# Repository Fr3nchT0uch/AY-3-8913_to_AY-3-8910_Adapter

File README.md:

# AY-3-8913 to AY-3-8910 Adapter

A simple adapter to replace the AY-3-8913 with the AY-3-8910 (or the YM2149)

## Why to replace the AY-3-8913 ?
If you've read this article https://www.fenarinarsa.com/?p=3183, you know that there's a chance your Mockingboard with AY-3-8913 will sound *weird* under certain circumstances.

Here a short video to hear the difference between a faulty AY-3-8913 and an AY-3-8910 in action (featuring Digidream 2): https://www.youtube.com/watch?v=_qslugOY2Dw

That's why we decided to do an adapter to easily replace the AY-3-8913 with the AY-3-8910 (or the YM2149) which does not suffer from the same issue and is more readily available.
We have made several designs giving you the choice for your use!
And they can of course be used as a basis for your own project! 

**Note about the Phasor Card**: these adapters are designed to be used primarily on a *Mockingboard*. For the *Phasor*, as there are 4 AY-3-8913s potentially to be replaced, it will probably be necessary to use a *daughter board* as adapter. This is beyond the scope of this project (for now...)

## Credits:  
Original idea: French Touch (grouik/fenarinarsa)  
http://fr3nch.t0uch.free.fr/  
Final design (and all the hard work!): Mr Jean-Fred  
https://github.com/Jean-Fred64

*French Touch would especially like to thank Mr Jean-Fred, without whom this project would never have been possible. It's thanks to him that an embryonic schematic was transformed into a viable project!*

## License:
GNU GENERAL PUBLIC LICENSE 3

## Reference:
Datasheets:  
AY-3-8910: https://map.grauw.nl/resources/sound/generalinstrument_ay-3-8910.pdf  
YM2149: http://www.ym2149.com/ym2149.pdf  

Mockingboard Info:  
https://en.wikipedia.org/wiki/Mockingboard
https://www.reactivemicro.com/product/mockingboard-assembled-or-kit/

Manufacturing PCB:  
https://www.kicad.org/  
https://jlcpcb.com/  
https://www.pcbway.com/

----  
## PCB designs:

## "Angle" version for Mockingboard (Two different PCBs for each AY-3-8913)

**LEFT** for *top* AY-3-8913:

**RIGHT** for *bottom* AY-3-8913:

- to replace one or **two** AY-3-8913 on your Mockingboard.
- you must use each version for the TOP and BOTTOM AY-3-8913 on your Mockbingboard.
- note: pay attention to the insertion direction of the AY-3-8910 on the adapter.

----  

## "Triangle" version for Mockingboard (A single PCB for the two AY-3-8913s)

- alternative (and ultimate) version to replace the TWO AY-3-8913 on the Mockingboard on the same board.

----
## "Normal" general version

- to replace only **one** AY-3-8913 on the Mockingboard (the **bottom** one only!).
- to replace the AY-3-8913 on other machines (for example: some old Pinball *soundcards*).
- note: pay attention to the insertion direction of the AY-3-8910 on the adapter.

- **WARNING**: do not use this model if you want to replace the **TWO** AY-3-8913s on your Mockingboard because you will not be able to close the Apple II cover! Use the other designs instead!

## Audio Output:

Each PCD design has an **Audio Output** (pins) for direct connection to the AY-3-8910/YM2149 without using the Mockingboard amplification part. This allows for much better quality with a line level output.

To be heard here: https://www.youtube.com/watch?v=SWxKD_74ifs

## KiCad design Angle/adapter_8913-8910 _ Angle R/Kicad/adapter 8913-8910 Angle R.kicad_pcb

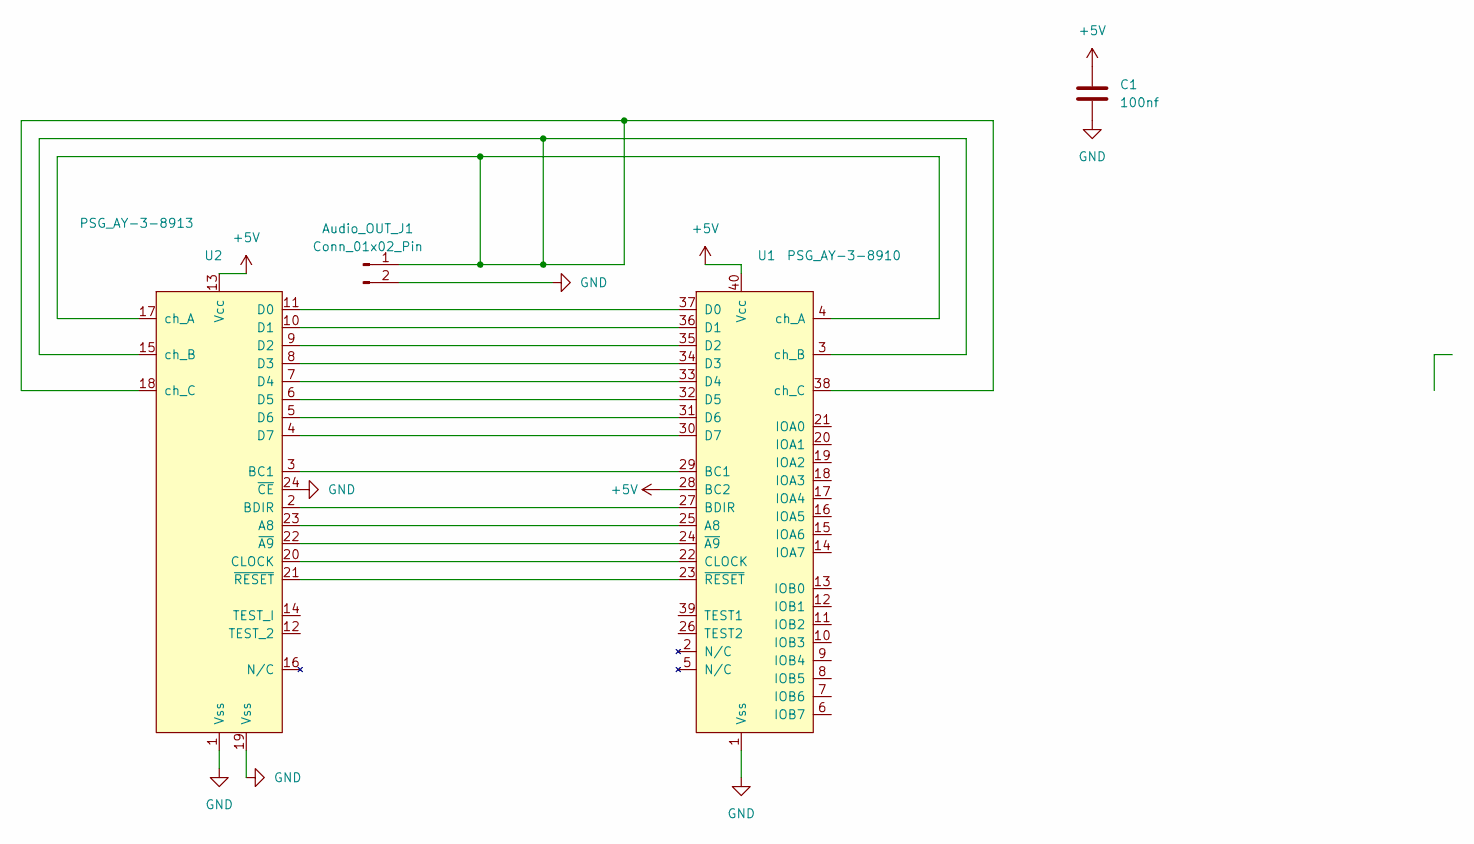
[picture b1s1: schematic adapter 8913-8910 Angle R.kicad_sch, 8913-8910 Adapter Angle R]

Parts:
Audio_OUT_J1: Conn_01x02_Pin; PinHeader_1x02_P2.54mm_Vertical
C1: 100nf; C_0805_2012Metric_Pad1.18x1.45mm_HandSolder
U1: PSG_AY-3-8910; DIP-40_W15.24mm_Socket
U2: PSG_AY-3-8913; DIP-24_W15.24mm_LongPads

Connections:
+5V: C1.1, U1.28 (BC2), U1.40 (Vcc), U2.13 (Vcc)
GND: Audio_OUT_J1.2, C1.2, U1.1 (Vss), U2.1 (Vss), U2.19 (Vss), U2.24 (~CE)
unnamed: Audio_OUT_J1.1, U1.3 (ch_B), U1.4 (ch_A), U1.38 (ch_C), U2.15 (ch_B), U2.17 (ch_A), U2.18 (ch_C)
unnamed: U1.25 (A8), U2.23 (A8)
unnamed: U1.29 (BC1), U2.3 (BC1)
unnamed: U1.27 (BDIR), U2.2 (BDIR)
unnamed: U1.22 (CLOCK), U2.20 (CLOCK)
unnamed: U1.37 (D0), U2.11 (D0)
unnamed: U1.36 (D1), U2.10 (D1)
unnamed: U1.35 (D2), U2.9 (D2)
unnamed: U1.34 (D3), U2.8 (D3)
unnamed: U1.33 (D4), U2.7 (D4)
unnamed: U1.32 (D5), U2.6 (D5)
unnamed: U1.31 (D6), U2.5 (D6)
unnamed: U1.30 (D7), U2.4 (D7)
unnamed: U1.24 (~A9), U2.22 (~A9)
unnamed: U1.23 (~RESET), U2.21 (~RESET)

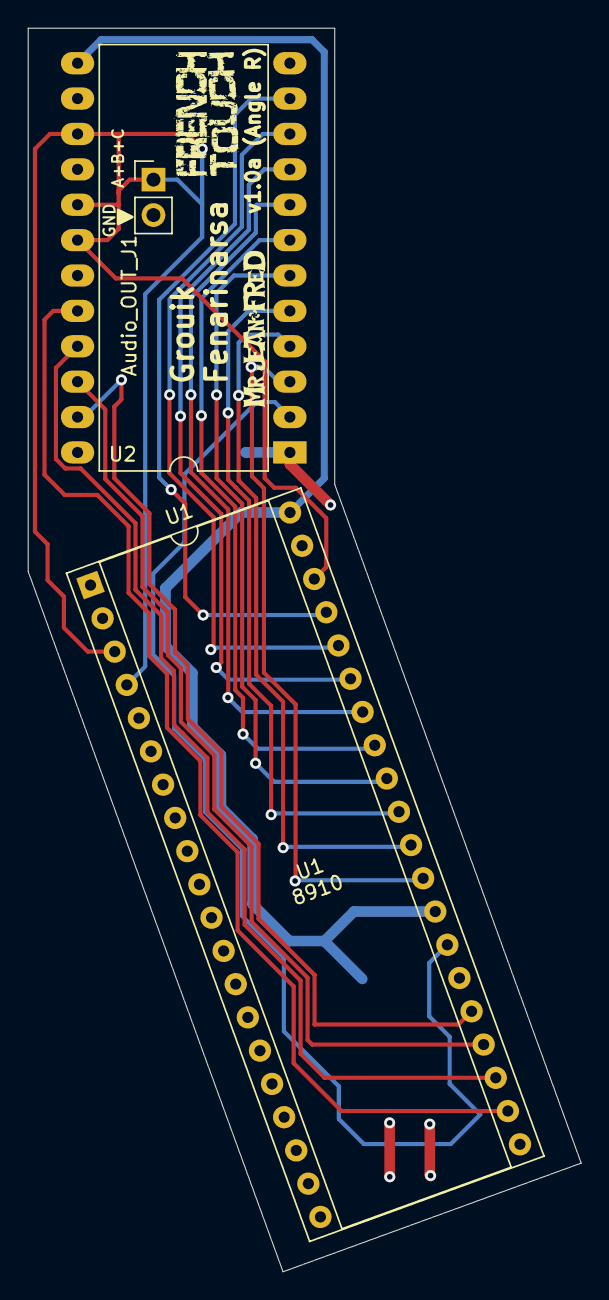
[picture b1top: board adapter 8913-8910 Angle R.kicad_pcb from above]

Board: 2 copper layers, 39.7 x 89.3 mm, 4 parts (1 on the bottom side), 17 nets.

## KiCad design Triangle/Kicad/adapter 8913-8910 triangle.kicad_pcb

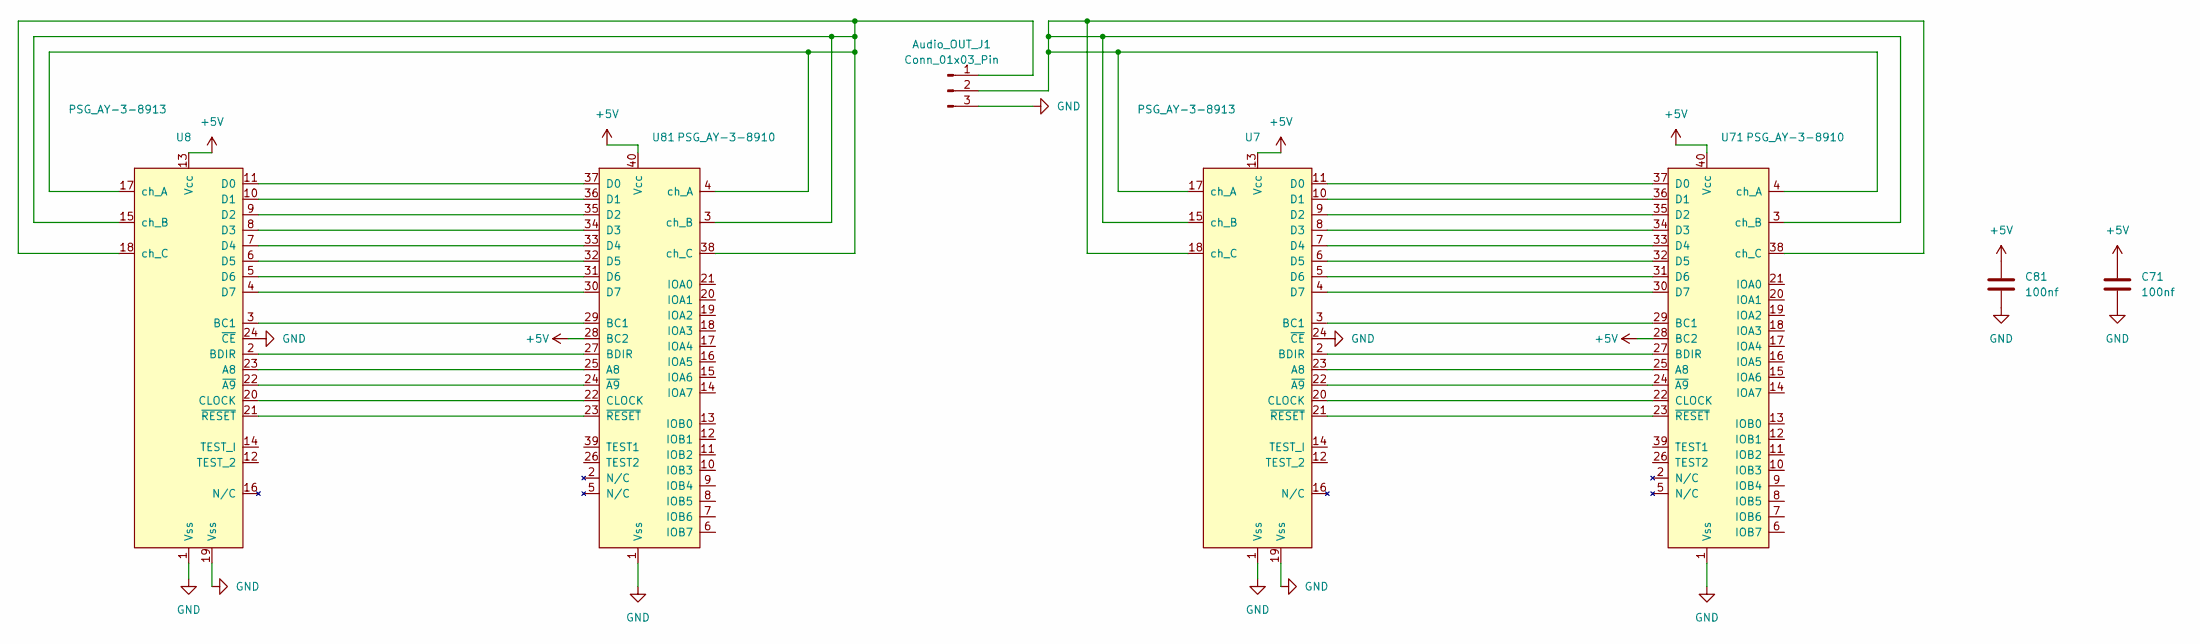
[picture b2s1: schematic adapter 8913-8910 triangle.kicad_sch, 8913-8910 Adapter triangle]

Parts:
Audio_OUT_J1: Conn_01x03_Pin; PinHeader_1x03_P2.54mm_Horizontal
C71, C81: 100nf; C_0805_2012Metric_Pad1.18x1.45mm_HandSolder
U7, U8: PSG_AY-3-8913; DIP-24_W15.24mm_LongPads
U71, U81: PSG_AY-3-8910; DIP-40_W15.24mm_Socket

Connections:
+5V: C71.1, C81.1, U7.13 (Vcc), U8.13 (Vcc), U71.28 (BC2), U71.40 (Vcc), U81.28 (BC2), U81.40 (Vcc)
GND: Audio_OUT_J1.3, C71.2, C81.2, U7.1 (Vss), U7.19 (Vss), U7.24 (~CE), U8.1 (Vss), U8.19 (Vss), U8.24 (~CE), U71.1 (Vss), U81.1 (Vss)
unnamed: Audio_OUT_J1.1, U8.15 (ch_B), U8.17 (ch_A), U8.18 (ch_C), U81.3 (ch_B), U81.4 (ch_A), U81.38 (ch_C)
unnamed: Audio_OUT_J1.2, U7.15 (ch_B), U7.17 (ch_A), U7.18 (ch_C), U71.3 (ch_B), U71.4 (ch_A), U71.38 (ch_C)
unnamed: U7.23 (A8), U71.25 (A8)
unnamed: U7.3 (BC1), U71.29 (BC1)
unnamed: U7.2 (BDIR), U71.27 (BDIR)
unnamed: U7.20 (CLOCK), U71.22 (CLOCK)
unnamed: U7.11 (D0), U71.37 (D0)
unnamed: U7.10 (D1), U71.36 (D1)
unnamed: U7.9 (D2), U71.35 (D2)
unnamed: U7.8 (D3), U71.34 (D3)
unnamed: U7.7 (D4), U71.33 (D4)
unnamed: U7.6 (D5), U71.32 (D5)
unnamed: U7.5 (D6), U71.31 (D6)
unnamed: U7.4 (D7), U71.30 (D7)
unnamed: U7.22 (~A9), U71.24 (~A9)
unnamed: U7.21 (~RESET), U71.23 (~RESET)
unnamed: U8.23 (A8), U81.25 (A8)
unnamed: U8.3 (BC1), U81.29 (BC1)
unnamed: U8.2 (BDIR), U81.27 (BDIR)
unnamed: U8.20 (CLOCK), U81.22 (CLOCK)
unnamed: U8.11 (D0), U81.37 (D0)
unnamed: U8.10 (D1), U81.36 (D1)
unnamed: U8.9 (D2), U81.35 (D2)
unnamed: U8.8 (D3), U81.34 (D3)
unnamed: U8.7 (D4), U81.33 (D4)
unnamed: U8.6 (D5), U81.32 (D5)
unnamed: U8.5 (D6), U81.31 (D6)
unnamed: U8.4 (D7), U81.30 (D7)
unnamed: U8.22 (~A9), U81.24 (~A9)
unnamed: U8.21 (~RESET), U81.23 (~RESET)

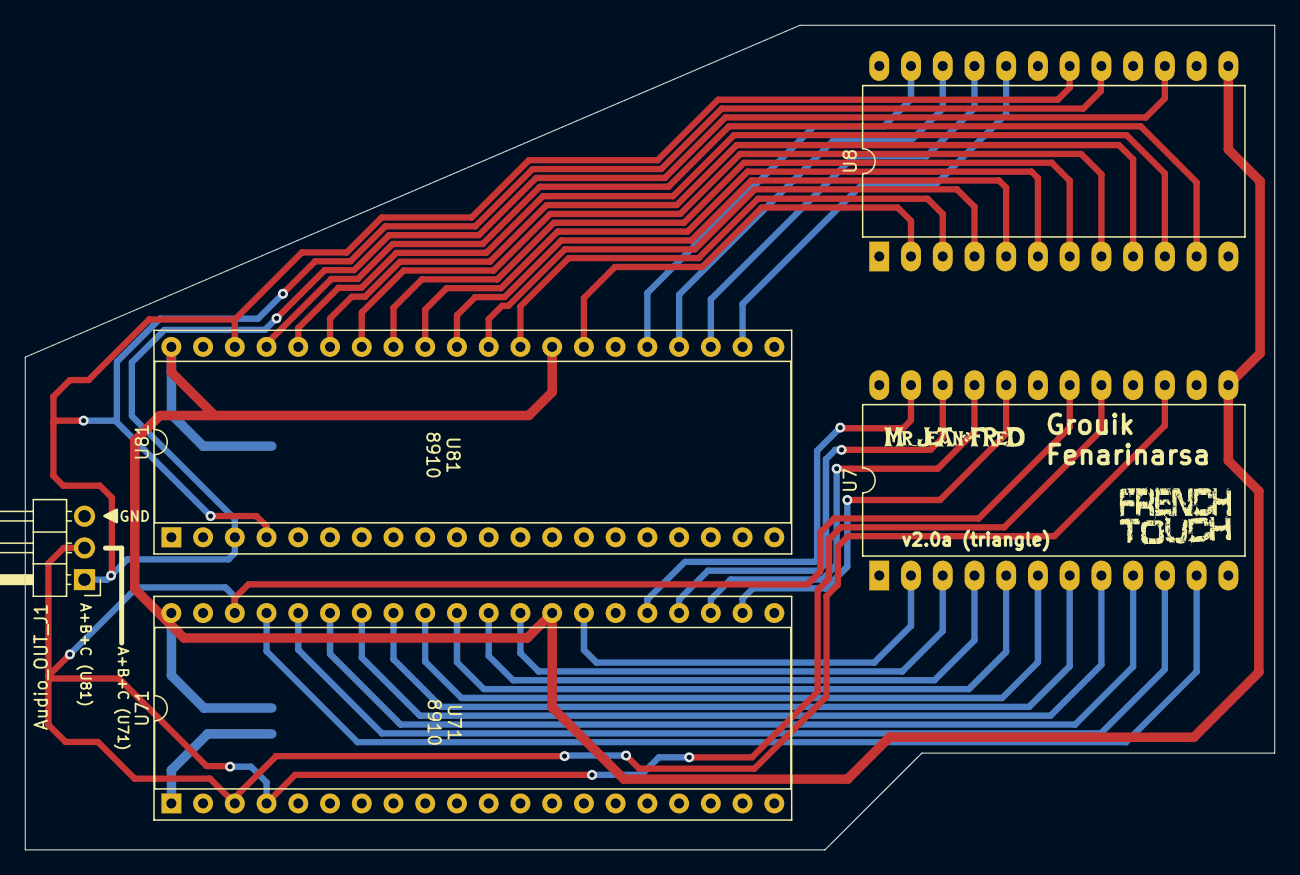
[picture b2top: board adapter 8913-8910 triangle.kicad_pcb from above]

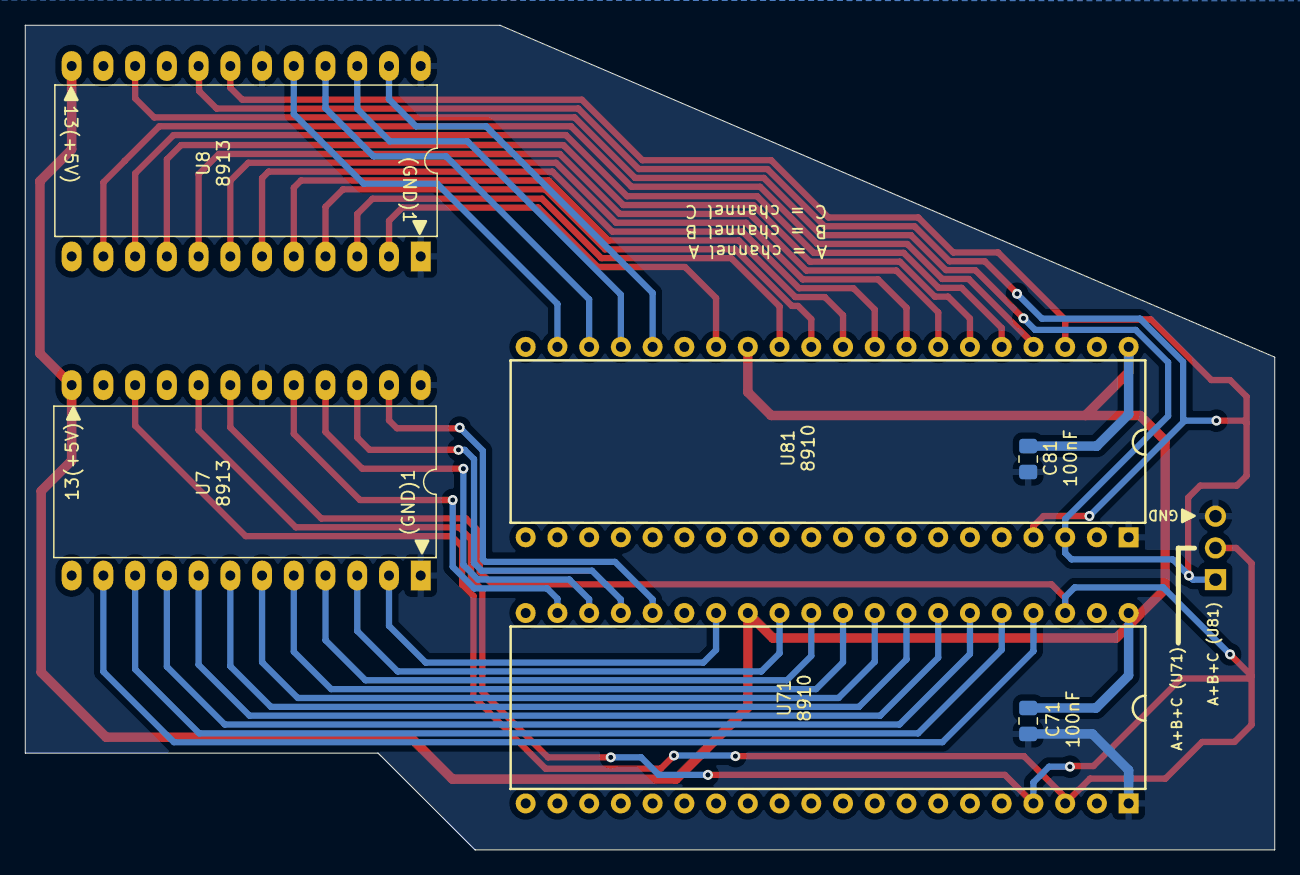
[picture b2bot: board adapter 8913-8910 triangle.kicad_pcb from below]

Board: 2 copper layers, 100.0 x 66.0 mm, 7 parts (2 on the bottom side), 32 nets.

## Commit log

2024-05-26 cleanup
2024-07-13 Readme updated. Image added.
2024-07-14 readme correction
2024-07-16 readme final version
2024-07-16 readme release version
2024-07-19 readme updated (audio output)
2024-07-19 readme updated (link to audio output video)
